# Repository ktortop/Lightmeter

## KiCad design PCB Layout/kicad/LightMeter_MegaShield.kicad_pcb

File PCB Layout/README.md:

# EVEI Light Meter – Arduino Mega 2560 shield (rev B)

Two-layer carrier shield that replaces the hand-wired proto shield. Generated from
`latest_version_of_lightmeter.ino` (pin map) and the Final Design Review slides (part list, wiring), and
checked against the team's current sketch, `Lightmeter_Week8.ino` in this repo (same pins; its `setLED()` sets the LED wiring).
No sketch was modified. Rev B needs a two-line firmware change for the GPS LED (see "Rev B changes"). Rev A is kept in `archive/revA/`.

Board: 90.7 x 102.1 mm with a 1.9 x 14 mm notch over the Mega's barrel jack, 2 layers, 1 oz copper, min track 0.3 mm (signals) / 0.6 mm (power), vias 0.8/0.4 mm (tented), copper at least 0.4 mm from every edge.
ERC: 0 violations. DRC: 0 errors, 0 warnings, 0 unconnected (schematic parity checked).

## Rev B changes

| Change | Detail |
|---|---|
| Second lux sensor port | J10, JST-XH 4 pin, same pinout as LUX1: GND · 5V · SDA · SCL. |
| I2C multiplexer | U3, PCA9548A (SOIC-24W, address 0x70). Needed because the TSL2591 has a fixed address (0x29), so two of them cannot share one bus. LUX2 is on mux channel 0 with 10k pull-ups (R11, R12). |
| Encoder port | J11, JST-XH 4 pin: GND · 5V · A · B. A goes to D2 (INT4), B to D3 (INT5), the two free hardware interrupts. |
| Encoder input conditioning | 10k pull-ups (R14, R15) so open-collector hall encoders work; 1k series + 1nF (R16/C10, R17/C11) filters cable noise and limits current if a pin is ever driven by mistake. |
| GPS status LED moved | D2/D3 to D4/D7, to free the interrupt pins for the encoder. |
| LEDs are common-cathode | Since Week 5 the sketch's `setLED()` drives a die by writing its pin HIGH (YELLOW = both HIGH, OFF = both LOW; the Week 5 comment says this fixed YELLOW and OFF being swapped on the real LEDs). So the LED connectors now give GND on pin 1 (common cathode), and each `*_red` pin drives the red die, each `*_green` pin the green die. All four states (green, red, yellow, off) show correctly with Week 8 as written. Rev A had 5V on pin 1 (common anode), which would have swapped YELLOW and OFF. |
| Barrel-jack notch | The Mega's DC jack (11 mm tall) reaches 0.4 mm under the rev A edge, higher than the 8.5 mm header gap. The bottom-left corner is notched to x = 12.9 mm, and the Mega hole beside the jack is left off (five Mega holes plus H1/H2 remain). |
| Regulator output cap | C2 is a 22 µF tantalum (EIA-3528-B). The AMS1117 needs some output-capacitor ESR to stay stable; a plain ceramic can make it oscillate. |
| SD chip-select pull-up | R18, 10k to 5V on the Mega side of the level shifter, so the card stays deselected while the Mega resets or is being programmed. |
| Nothing under the IMU | Track/via keepout under the BNO055. DC current in nearby traces bends the magnetometer and the heading. Nearest 5V trace is now 11 mm from the IMU centre. |
| Hand-soldering and fab | Thermal reliefs on all ground pads, vias tented, all silkscreen at least 0.15 mm, decoupling caps within 6 mm of their pins. |
| Board size | 13 mm taller (new top row). microSD moved up so its slot is still at the top edge. |

LUX1 stays on the main I2C bus. The mux powers up with every channel off, so LUX1 and the LCD work exactly as before.

### Firmware changes needed (sketch not edited)

1. GPS LED pins, in the constants block:
   ```cpp
   const int gps_red   = 4;   // was 2
   const int gps_green = 7;   // was 3
   ```
   **Make this change before plugging an encoder in.** The old sketch drives D2/D3 as outputs. The 1k series resistors limit the current, but the LED will not work until the pins are changed.

2. Reading the second lux sensor:
   ```cpp
   Adafruit_TSL2591 tsl2 = Adafruit_TSL2591(2592);
   void muxSelect(uint8_t ch) { Wire.beginTransmission(0x70); Wire.write(ch); Wire.endTransmission(); }
   // setup:  muxSelect(0x01); tsl2.begin(); tsl2.setGain(TSL2591_GAIN_LOW); muxSelect(0x00);
   // loop:   muxSelect(0x01); uint32_t lum2 = tsl2.getFullLuminosity(); muxSelect(0x00);
   ```
   Always write 0x00 afterwards. While channel 0 is open, both sensors answer at 0x29.

3. Encoder: D2 and D3 are hardware interrupts, so either `attachInterrupt(digitalPinToInterrupt(2), isrA, CHANGE)` or the PJRC `Encoder` library (`Encoder enc(2, 3);`) works at full speed.

## Folder contents

| Path | What |
|---|---|
| `kicad/` | KiCad 10 project: schematic, PCB, project-local symbol + footprint libs. Open `LightMeter_MegaShield.kicad_pro`. |
| `docs/schematic.pdf` | Schematic (A2, single sheet; rev B additions on the right). |
| `docs/render_top.png`, `render_bottom.png`, `render_3d.png` | 3D renders. |
| `docs/pcb_top.pdf`, `pcb_bottom.pdf` | Copper + silk plots. |
| `docs/BOM.csv` | Bill of materials (grouped). |
| `docs/LightMeter_MegaShield.step` | 3D model for the cart CAD. |
| `fab/LightMeter_MegaShield_gerbers.zip` | Gerbers + Excellon drills, ready for JLCPCB/PCBWay/OSH Park. `-pos.csv` is the SMD pick-and-place file. |
| `generator/` | Python scripts that generated everything (design.py holds the netlist and placement). Re-run if you change a pin. |

## How the Mega is "embedded"

The Arduino Mega 2560 plugs into the underside of this board through the standard Mega
stacking-header pattern (all 92 header and ICSP pads, checked pad by pad against KiCad's own
Arduino Mega template). Five of the Mega's six mounting holes are duplicated on the shield so the two
boards can be bolted together with M3 standoffs. The board is wider than the Mega on top (a
35 mm extension above the top header row) where all the cable connectors and the microSD live,
so no cable crosses the Mega. The left edge stops at x = 11 mm to clear the USB-B jack, and steps to 12.9 mm over the barrel jack.

Plain male headers (see "Assembly and soldering") or a Mega stacking header set both fit. The ICSP pads are on the
footprint but are left unconnected; do not fit a header there.

## What is on the board vs. on a cable

| Function | How | Mega pins (from the sketch) |
|---|---|---|
| Adafruit Ultimate GPS v3 (746) | Soldered onto the board on a 1x9 header (pin order PPS·VIN·GND·RX·TX·FIX·VBAT·EN·3.3V verified from Adafruit's board file) + two M2.5 holes | Serial1: D18→GPS RX, D19←GPS TX |
| microSD | Real socket on the board (Hirose DM3AT push-push), own AMS1117-3.3 regulator (22 µF tantalum output cap), 74LVC125A level shifter on MOSI/SCK/CS, 10k pull-ups on CS/DAT0/DAT1/DAT2 | HW SPI D50/51/52, CS D53 |
| Adafruit BNO055 (2472, non-STEMMA) | Soldered onto the board (1x6 + 1x4 headers, positions from Adafruit's board file) + four M2.5 holes. UART mode: PS1 tied to breakout 3Vo through solder jumper JP1 (bridged by default) | Serial2: D16→BNO SCL pin (UART RX), D17←BNO SDA pin (UART TX) |
| 20x4 LCD (I2C backpack) | J2, JST-XH 4 pin: GND · 5V · SDA · SCL | D20/D21 |
| TSL2591 lux sensor | J3, JST-XH 4 pin: GND · 5V · SDA · SCL (same pinout as LCD, cables interchangeable) | D20/D21 |
| Status LED 1 (GPS) | J4, JST-XH 3 pin: GND (common cathode) · RED · GREEN, 220 Ω series resistors on board | red D4 (`gps_red`), green D7 (`gps_green`) |
| Status LED 2 (LUX) | J5, same | red D5 (`lux_red`), green D6 (`lux_green`) |
| Status LED 3 (IMU) | J6, same | red D8 (`imu_red`), green D9 (`imu_green`) |
| Sleep button | J7, JST-XH 3 pin: GND · SW · 5V (5V for the arcade-button lamp, optional). 100 nF debounce cap on board, uses INPUT_PULLUP | D10 |
| Log-toggle button | J8, same | D11 |
| Force-log button | J9, same | D12 |

LED polarity matches `setLED()` in Week 5-8: output HIGH = die on, both HIGH = yellow, both LOW = off. Wire each LED's common cathode (usually the middle leg of a 3-leg bi-colour LED; check its datasheet) to pin 1, its red leg to pin 2 and its green leg to pin 3, as the silkscreen says (`GND R G`). Two separate red and green LEDs work too: both cathodes to pin 1. Common-anode LEDs will not work on this board.
Buttons go to GND (active LOW), matching `digitalRead(...) == LOW`.

### Cable pinouts (board side is always pin 1 = square pad = left end of the label)

| Port | Pin 1 | Pin 2 | Pin 3 | Pin 4 | Far end |
|---|---|---|---|---|---|
| LCD (J2) | GND | 5V | SDA | SCL | I2C backpack: GND, VCC, SDA, SCL (same order) |
| LUX1 (J3), LUX2 (J10) | GND | 5V | SDA | SCL | Adafruit TSL2591: GND, VIN, SDA, SCL (leave 3Vo and INT unconnected) |
| ENCODER (J11) | GND | 5V | A | B | encoder GND, VCC (5 V encoders only), channel A, channel B |
| GPS/LUX/IMU LED (J4-J6) | GND | red | green | | LED common cathode, red anode, green anode (no resistor needed, 220 Ω is on the board) |
| SLEEP/LOG/FORCE (J7-J9) | GND | SW | 5V | | switch between SW and GND; lamp (optional) between 5V and GND |

**Do not swap LED and button cables.** Both are 3-pin JST-XH, so either fits either port. A button in an LED port is harmless, but an LED in a button port puts 5 V straight onto its green leg with no resistor and burns it out. Label or colour-code the six 3-pin cables. The 4-pin ports are safe to mix up: GND and 5V are on the same pins everywhere.

## Assembly and soldering

Checked against the layout: all parts are on the top side, nothing sits under the GPS or IMU breakouts, no part is in
the path of the Mega header bodies, and the surface-mount parts are all soldered before anything tall goes on
(the closest, R14, is 0.8 mm from C5). Ground pads use thermal reliefs so they take solder with an ordinary iron.
No tracks run under any screw head, washer or standoff. The only pad gap under 0.4 mm is the microSD's unused
card-detect pad (pin 9), left unconnected so a bridge there does no harm.

**Tools:** temperature-controlled iron with a 1–1.6 mm chisel tip, 0.5 mm flux-core solder, a flux pen,
solder wick, fine tweezers, a magnifier or phone camera, a multimeter.

**Headers to buy:** plain male headers are recommended, since nothing stacks on top of this shield:
two 1x40 strips (cut into 1x10, 5 x 1x8) plus one 2x18 (or a 2x20 cut down). They hold the shield
2.5 mm higher than stacking headers do, which adds clearance over the Mega's USB jack, barrel jack and
USB-chip ICSP pins. A "Mega stacking header set" also fits; no part is in the way of either.

### Buy list (not on the BOM)

| Item | Qty | Notes |
|---|---|---|
| Male pin headers, 2.54 mm, 1x40 | 2 | cut into 1x10 + 5 x 1x8 for the Mega |
| Male pin header, 2.54 mm, 2x18 (or 2x20 cut down) | 1 | Mega double row |
| M2.5 nylon hex standoffs, 5 mm | 2 | GPS (the coin-cell holder needs the height) |
| M2.5 nylon screws, 6 mm | 4 | GPS (2 standoffs, both ends) |
| M2.5 nylon screws + nuts | 4 | IMU (optional, the headers hold it) |
| M3 nylon standoffs, 11 mm, + screws | up to 5 | Mega to shield (optional); 11 mm = 8.5 mm female header + 2.5 mm male header spacer |
| JST-XH housings XHP-4 / XHP-3 | 4 / 6 | cable ends |
| JST-XH crimp contacts SXH-001T-P0.6 | about 40 | needs a JST-type crimper (for example Engineer PA-09); pre-crimped XH leads avoid the tool |
| 5 mm bi-colour red/green LED, common cathode | 3 | or separate red + green LEDs |
| microSD card, 32 GB or less, FAT32 | 1 | the SD library only reads FAT16/FAT32 |
| CR1220 coin cell | 1 | optional, keeps the GPS almanac for faster fixes |

### Solder order (smallest and hardest first)

1. **microSD socket (J1).** Hardest joint: 8 pins at 1.1 mm pitch that stick out only 0.5 mm past the
   metal shell. Flux the pads, place the socket, tack one shell tab, check alignment, solder all four shell
   tabs, then touch each signal pin with the tip of the iron. Inspect for bridges and wick any away.
2. **SOIC chips, U1 (74LVC125A) and U3 (PCA9548A).** Match the dot on the chip to the pin-1 mark on the
   silkscreen. Tack one corner pin, check both rows are on their pads, solder the opposite corner, then
   the rest. Flux and wick fix bridges.
3. **Regulator U2 (AMS1117, SOT-223).** The large tab needs more heat: use a bigger tip or more dwell time.
4. **0805 resistors and capacitors.** Do one value at a time from the BOM: 220 Ω (R1–R6), 10 kΩ
   (R7–R15, R18), 1 kΩ (R16, R17), 100 nF (C3, C4, C6–C9), 1 nF (C10, C11), 10 µF (C1). Tin one pad,
   slide the part in with tweezers, then solder the other end.
5. **C2 tantalum.** Polarized: the stripe on the part goes to the side marked on the silkscreen (+3.3 V).
6. **Short test before anything else.** With the multimeter, check there is no short between 5V and GND,
   or between 3.3V and GND. It is much easier to fix now.
7. **C5 electrolytic** (100 µF/16 V, 6.3 mm or 5 mm diameter). Long leg (+) to the square pad, stripe (–) to the round pad.
8. **JST connectors J2–J11.** Push fully down; the outline on the silkscreen shows which way the housing faces.
9. **Mega headers.** Plug the headers into the Mega first, lay the shield on top, then solder from the top.
   This guarantees they line up with the Mega. Unplug the shield before the next steps.
10. **GPS breakout.** The CR1220 holder on the GPS's underside is taller than a header's 2.5 mm plastic spacer, so
    the GPS sits on 5 mm standoffs. Screw the two 5 mm nylon standoffs to the shield (holes at the far end from the
    header). Push the **short** pins of the 1x9 header up into the GPS from below (plastic spacer against the GPS),
    lower the long pins through the shield, screw the GPS to the standoffs, then solder on top of the GPS and under
    the shield. About 1.9 mm of pin comes through the shield. Antenna (ceramic patch) faces up.
11. **IMU breakout.** Nothing on its underside, so the headers' own 2.5 mm spacers set the height: short pins into
    the IMU (1x6 and 1x4), long pins through the shield, solder both ends. Nylon hardware only if you add screws
    (steel or brass near the magnetometer affects the heading). The +X arrow on the BNO055 must point along
    the cart's direction of travel when the board is mounted.
12. **Trim** the GPS and IMU header pins that stick out under the shield flush, so they cannot touch the Mega.
    Do **not** trim the Mega header pins: they are what plugs into the Mega.

JP1 needs no soldering: it ships bridged by a copper trace. Only cut it to move the IMU to I2C.

### First power-up

1. No cables plugged in. Connect the Mega to USB. Measure 5 V on any JST pin 2 (LCD/LUX) and 3.3 V on C4.
2. Feel U2, U1 and U3: none should be warm.
3. Change `gps_red = 4` and `gps_green = 7` in the sketch, upload, then plug in the LEDs, LCD, lux
   sensor and buttons. Insert the SD card last.
4. Expected at boot (Week 8): all three LEDs red; IMU turns green when the BNO055 answers, GPS turns yellow while it
   waits for a fix, LUX turns green when the TSL2591 answers.

### Other notes

- IMU orientation matters. Week 8's level check uses roll only (`eulY`, rotation about the BNO's Y axis), and the
  heading and forward acceleration (`linX`) assume the BNO's +X axis points along the cart's travel. Mount the board
  so the +X arrow printed on the BNO055 breakout points forward (the shield silkscreen says so). If the board has to be
  mounted 90° off, swap roll and pitch (and use `linY`) in the sketch instead.
- MISO comes back to D50 at 3.3 V without shifting, the same as the Adafruit SD breakout used today. The ATmega2560
  reads HIGH from 3.0 V, so the margin is small; real cards drive close to 3.3 V at this light load. If a card is
  flaky, try another brand before suspecting the board.
- Power budget from the Mega's 5 V rail: Mega about 80 mA, 20x4 LCD backlight about 100 mA, LEDs up to 80 mA (all
  yellow), SD card up to 100 mA while writing, GPS 30 mA, BNO055 12 mA, encoder and button lamps 20-60 mA:
  about 400-450 mA worst case. USB (500 mA fuse) or a 5 V supply into USB is fine. On the barrel jack use about 7 V:
  at 9 V the Mega's regulator dissipates about 1.8 W and will overheat.

## Design decisions / assumptions worth reviewing

- "Embedded Arduino" was implemented as a shield the Mega plugs into, not a bare ATmega2560 on
  the board. That keeps the USB bootloader, uses the Mega the team already has and is buildable
  by hand. A bare-chip version could follow once this one is proven.
- The IMU was placed on the board (not on a connector) because it must be rigidly fixed to the
  cart for the tilt check and it removes six jumper wires. If you want it remote, the header
  footprint accepts a cable instead.
- The Adafruit MicroSD breakout was replaced by an on-board socket and level shifter (its own
  circuit, copied). The Adafruit breakout is no longer needed.
- The cart-facing connectors are JST-XH because they lock and are cheap; the pin-order note is on
  the silkscreen next to every connector.
- Board outline, stacking-header positions and breakout footprints are from published board
  files, but nothing has been test-fitted physically. Print `docs/pcb_top.pdf` 1:1 and lay the
  Mega, the GPS and the IMU on it before ordering.

## Pre-order validation (final)

Automated: ERC 0, DRC 0 errors / 0 warnings, 0 unconnected, schematic-parity 0, netlist matches `generator/design.py` on all 42 nets.
`generator/audit.py` re-checks edge clearances, annular rings, decoupling distances, the IMU keepout and the LED mapping.

Against OSH Park's 2-layer rules: track 0.30 mm (min 0.152), clearance 0.20 mm (min 0.152), drill 0.40 mm (min 0.33),
annular ring 0.20 mm (min 0.178), copper to edge 0.40 mm (min 0.38). Gerber mask and drill files cross-checked against the board:
274 pad openings, 199 plated holes (147 pins + 52 vias), 13 unplated holes.
A second pass also ran DRC with every check enabled (only the expected Mega "no courtyard" and the 74LVC125 symbol's
DIP-only footprint filter came up), checked every net pin by pin against `design.py`, and checked the GPS, BNO055 and
Mega footprints against Adafruit's board files and KiCad's Arduino Mega template.

Check during the 1:1 paper test-fit, because only the physical parts can confirm them:
- the Mega's barrel jack clears the notch and the USB jack clears the left edge;
- the 6-pin ICSP header of the Mega's USB chip (near the USB jack) does not touch the underside (plain male headers give 2.5 mm more room; tape it if it touches);
- the GPS and IMU header pins are trimmed flush underneath so they cannot touch the Mega.

Not board issues, but decide before use:
- Power the Mega from USB (a USB power bank works) or about 7 V on the barrel jack; 9 V and above overheat its regulator at this load.
- Use nylon standoffs and screws near the IMU, not steel or brass.
- Long I2C cables to the LCD and lux sensors (over about 1 m) may need slower I2C (`Wire.setClock(50000)`).
- Arcade-button lamps are often rated 12 V; at 5 V they are dim but safe.

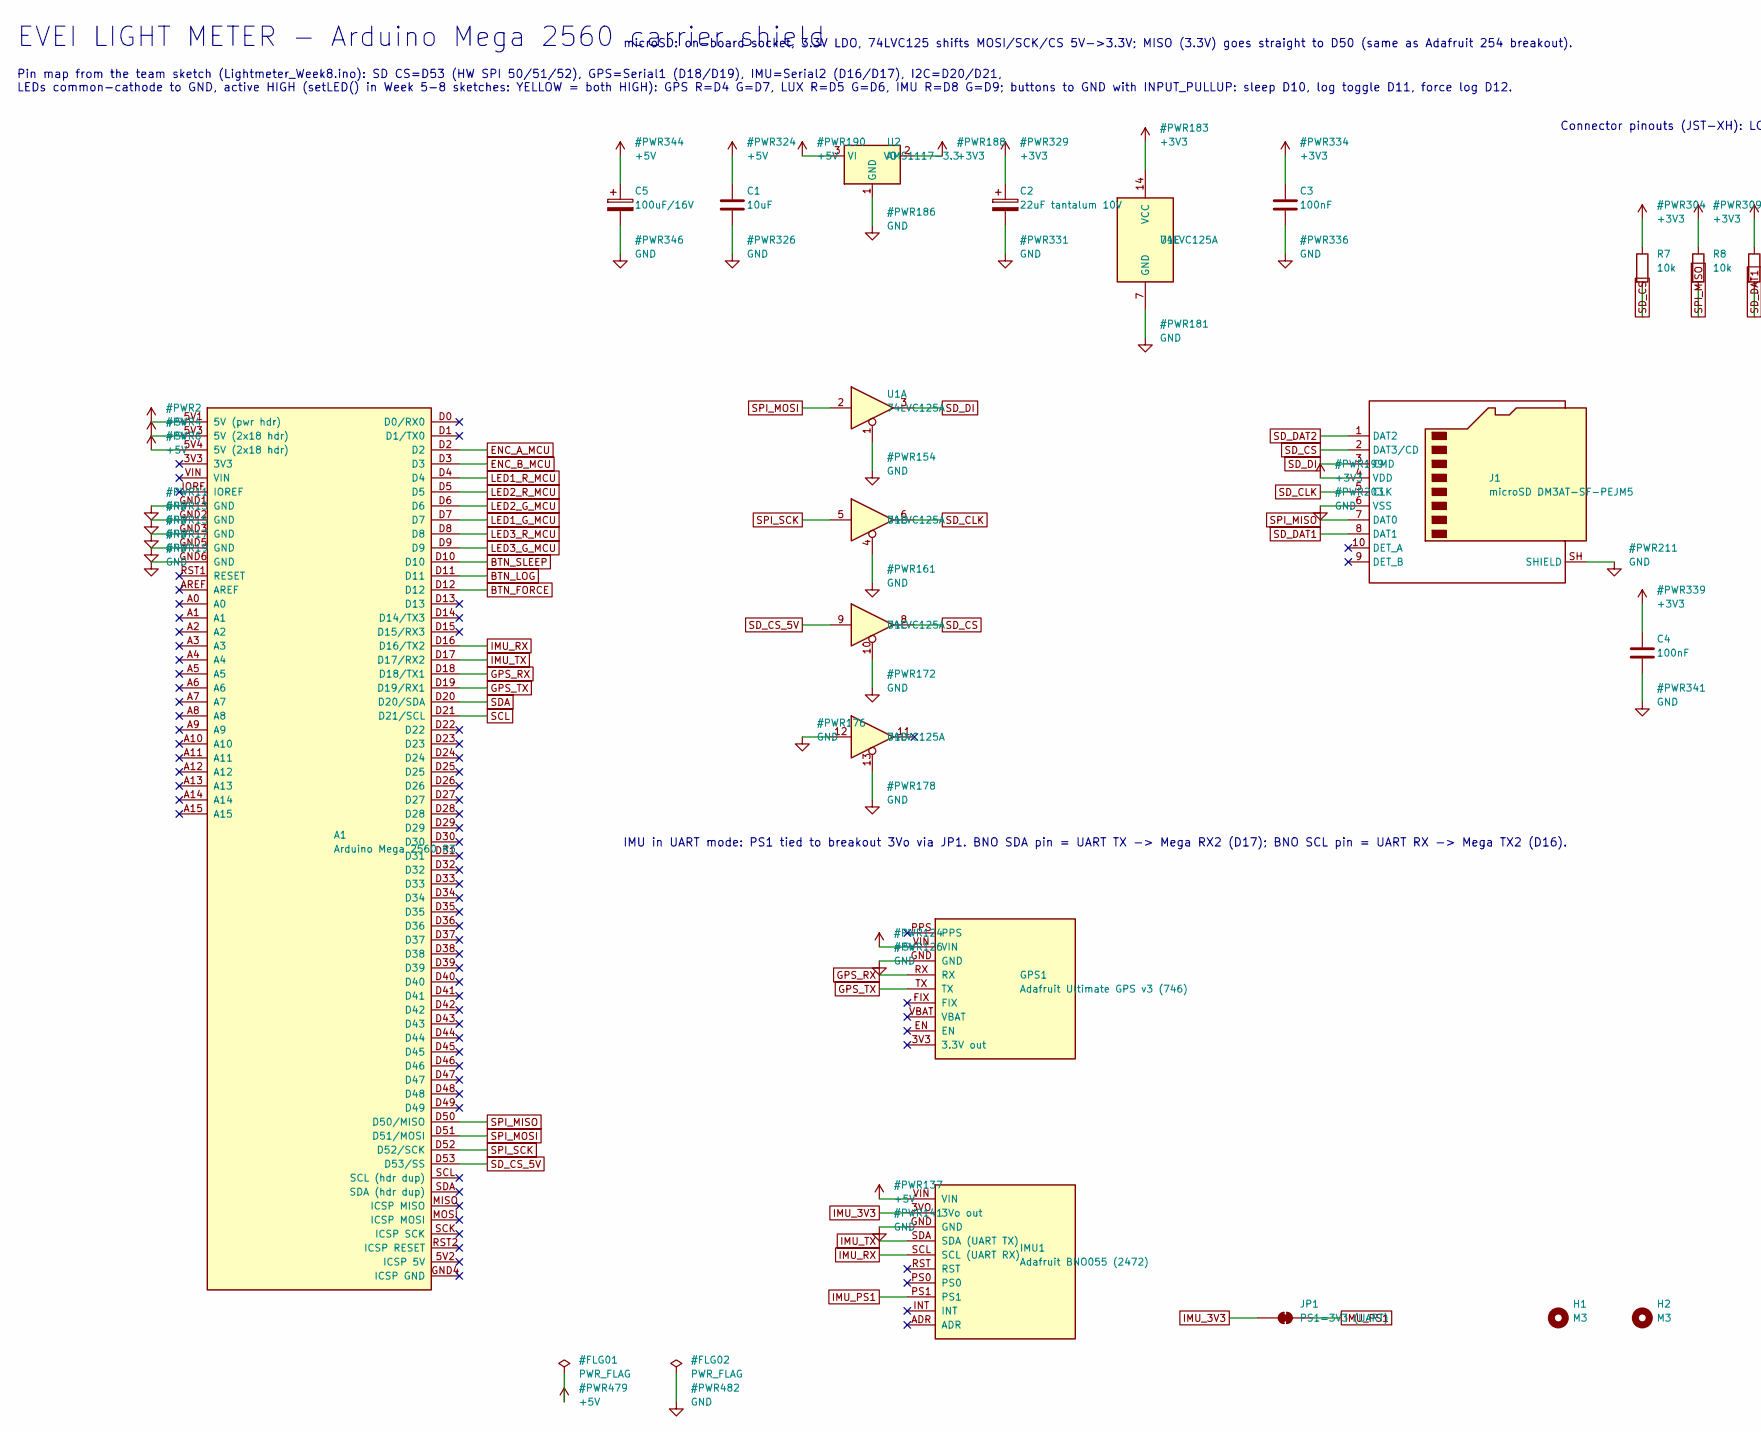
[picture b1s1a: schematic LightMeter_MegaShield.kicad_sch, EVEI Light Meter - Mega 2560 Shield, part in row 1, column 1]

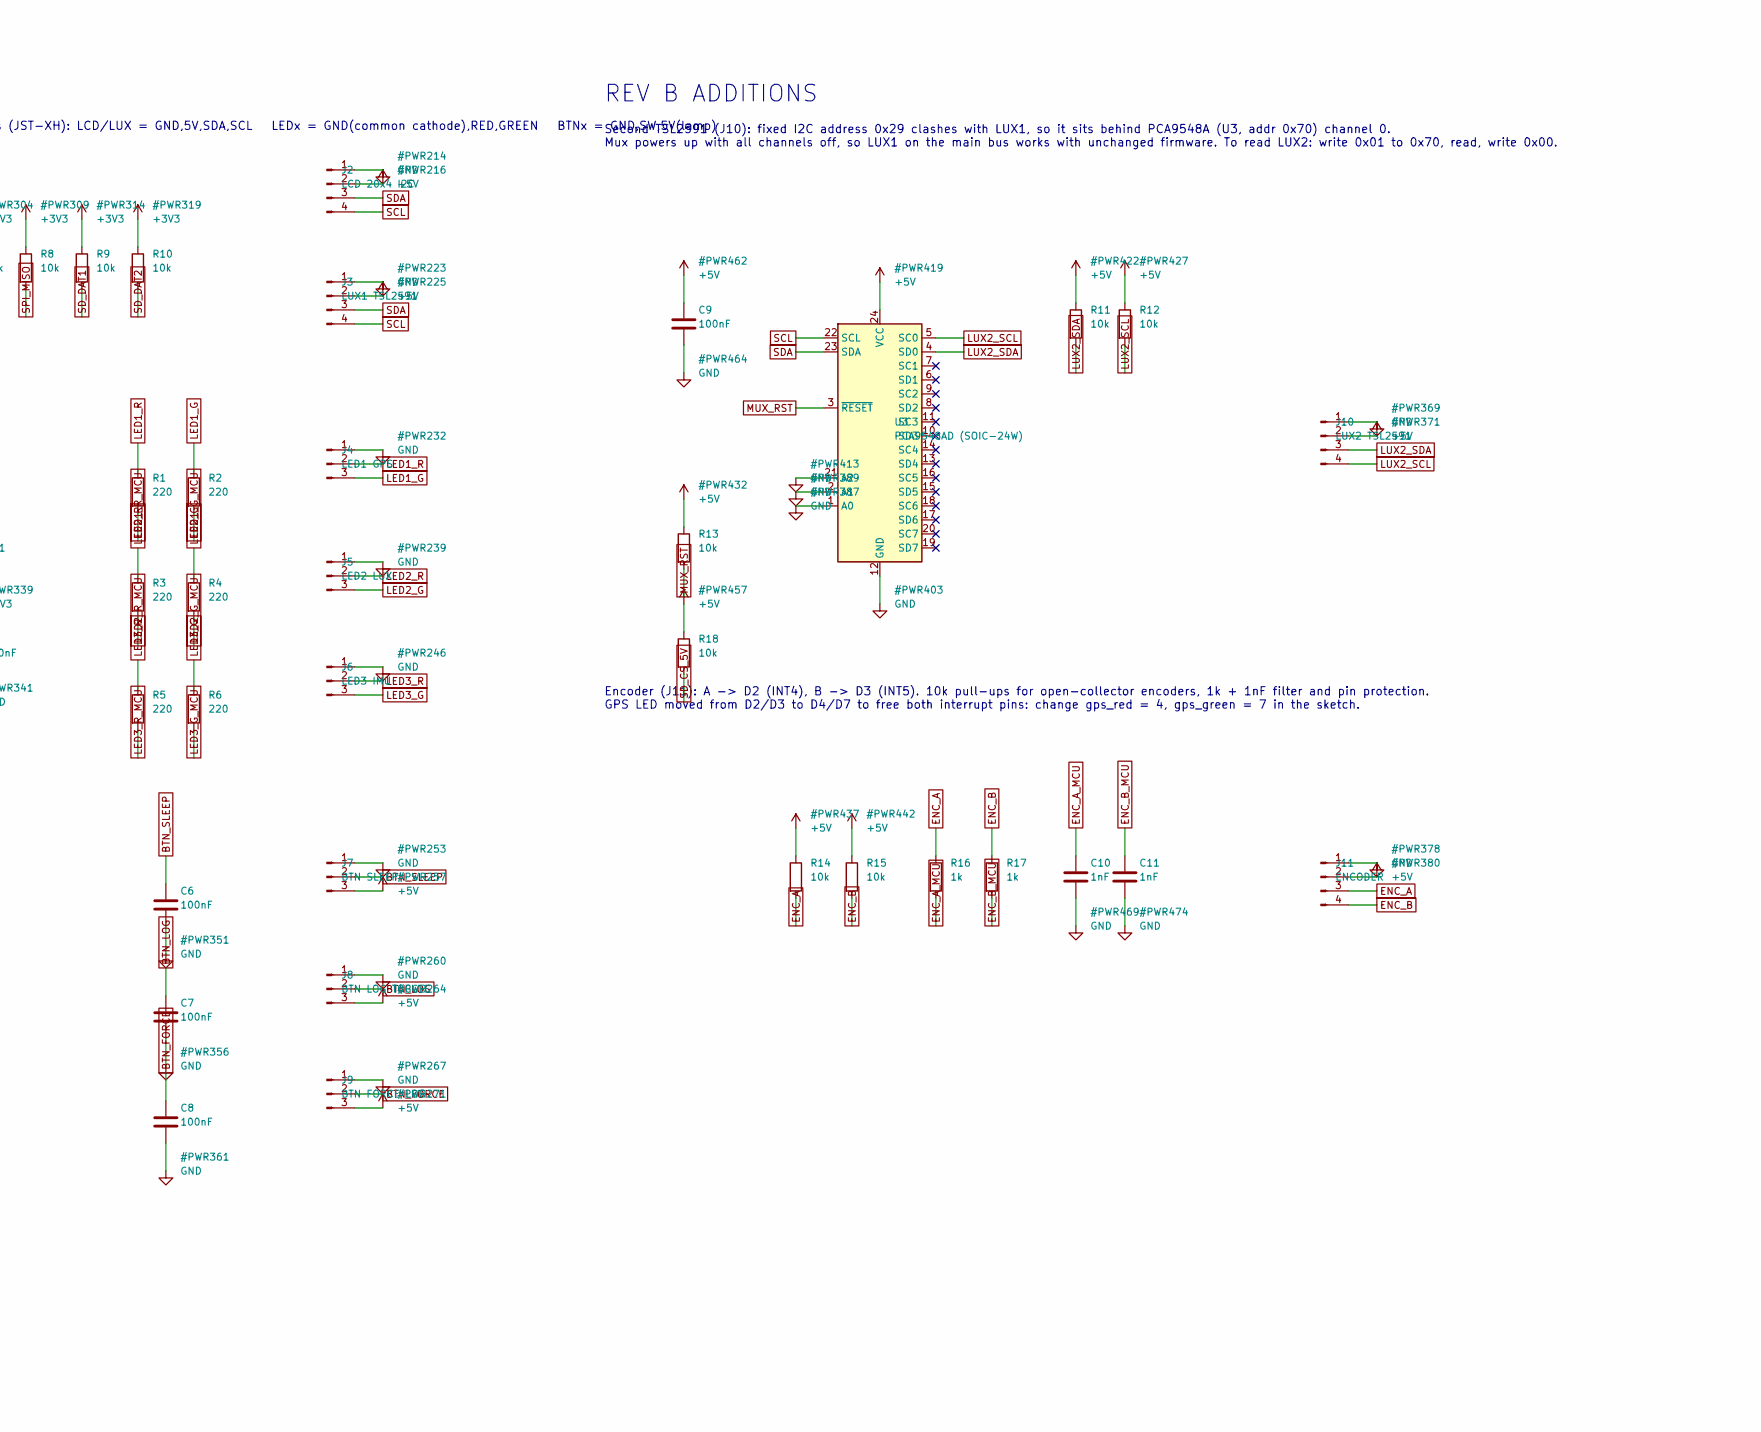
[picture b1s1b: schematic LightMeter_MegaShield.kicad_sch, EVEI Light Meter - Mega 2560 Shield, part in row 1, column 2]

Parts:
A1: Arduino Mega 2560 R3; Arduino_Mega2560_Shield
C1: 10uF; C_0805_2012Metric
C2: 22uF tantalum 10V; CP_EIA-3528-21_Kemet-B
C3, C4, C6, C7, C8, C9: 100nF; C_0805_2012Metric
C5: 100uF/16V; CP_Radial_D6.3mm_P2.50mm
C10, C11: 1nF; C_0805_2012Metric
GPS1: Adafruit Ultimate GPS v3 (746); Adafruit_UltimateGPS_v3
H1, H2: M3; MountingHole_3.2mm_M3
IMU1: Adafruit BNO055 (2472); Adafruit_BNO055_2472
J1: microSD DM3AT-SF-PEJM5; microSD_HC_Hirose_DM3AT-SF-PEJM5
J2: LCD 20x4 I2C; JST_XH_B4B-XH-A_1x04_P2.50mm_Vertical
J3: LUX1 TSL2591; JST_XH_B4B-XH-A_1x04_P2.50mm_Vertical
J4: LED1 GPS; JST_XH_B3B-XH-A_1x03_P2.50mm_Vertical
J5: LED2 LUX; JST_XH_B3B-XH-A_1x03_P2.50mm_Vertical
J6: LED3 IMU; JST_XH_B3B-XH-A_1x03_P2.50mm_Vertical
J7: BTN SLEEP; JST_XH_B3B-XH-A_1x03_P2.50mm_Vertical
J8: BTN LOG TOGGLE; JST_XH_B3B-XH-A_1x03_P2.50mm_Vertical
J9: BTN FORCE LOG; JST_XH_B3B-XH-A_1x03_P2.50mm_Vertical
J10: LUX2 TSL2591; JST_XH_B4B-XH-A_1x04_P2.50mm_Vertical
J11: ENCODER; JST_XH_B4B-XH-A_1x04_P2.50mm_Vertical
JP1: PS1=3V3 (UART); SolderJumper-2_P1.3mm_Bridged_RoundedPad1.0x1.5mm
R1, R2, R3, R4, R5, R6: 220; R_0805_2012Metric
R7, R8, R9, R10, R11, R12, R13, R14, R15, R18: 10k; R_0805_2012Metric
R16, R17: 1k; R_0805_2012Metric
U1: 74LVC125A; SOIC-14_3.9x8.7mm_P1.27mm
U2: AMS1117-3.3; SOT-223-3_TabPin2
U3: PCA9548AD (SOIC-24W); SOIC-24W_7.5x15.4mm_P1.27mm

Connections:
+3V3: C2.1, C3.1, C4.1, J1.4 (VDD), R7.1, R8.1, R9.1, R10.1, U1.14 (VCC), U2.2 (VO)
+5V: A1.5V1 (5V (pwr hdr)), A1.5V3 (5V (2x18 hdr)), A1.5V4 (5V (2x18 hdr)), C1.1, C5.1, C9.1, GPS1.VIN, IMU1.VIN, J2.2, J3.2, J7.3, J8.3, J9.3, J10.2, J11.2, R11.1, R12.1, R13.1, R14.1, R15.1, R18.1, U2.3 (VI), U3.24 (VCC)
BTN_FORCE: A1.D12, C8.1, J9.2
BTN_LOG: A1.D11, C7.1, J8.2
BTN_SLEEP: A1.D10, C6.1, J7.2
ENC_A: J11.3, R14.2, R16.1
ENC_A_MCU: A1.D2, C10.1, R16.2
ENC_B: J11.4, R15.2, R17.1
ENC_B_MCU: A1.D3, C11.1, R17.2
GND: A1.GND1 (GND), A1.GND2 (GND), A1.GND3 (GND), A1.GND5 (GND), A1.GND6 (GND), C1.2, C2.2, C3.2, C4.2, C5.2, C6.2, C7.2, C8.2, C9.2, C10.2, C11.2, GPS1.GND, IMU1.GND, J1.6 (VSS), J1.SH (SHIELD), J2.1, J3.1, J4.1, J5.1, J6.1, J7.1, J8.1, J9.1, J10.1, J11.1, U1.1, U1.4, U1.7 (GND), U1.10, U1.12, U1.13, U2.1 (GND), U3.1 (A0), U3.2 (A1), U3.12 (GND), U3.21 (A2)
GPS_RX: A1.D18 (D18/TX1), GPS1.RX
GPS_TX: A1.D19 (D19/RX1), GPS1.TX
IMU_3V3: IMU1.3VO (3Vo out), JP1.1 (A)
IMU_PS1: IMU1.PS1, JP1.2 (B)
IMU_RX: A1.D16 (D16/TX2), IMU1.SCL (SCL (UART RX))
IMU_TX: A1.D17 (D17/RX2), IMU1.SDA (SDA (UART TX))
LED1_G: J4.3, R2.1
LED1_G_MCU: A1.D7, R2.2
LED1_R: J4.2, R1.1
LED1_R_MCU: A1.D4, R1.2
LED2_G: J5.3, R4.1
LED2_G_MCU: A1.D6, R4.2
LED2_R: J5.2, R3.1
LED2_R_MCU: A1.D5, R3.2
LED3_G: J6.3, R6.1
LED3_G_MCU: A1.D9, R6.2
LED3_R: J6.2, R5.1
LED3_R_MCU: A1.D8, R5.2
LUX2_SCL: J10.4, R12.2, U3.5 (SC0)
LUX2_SDA: J10.3, R11.2, U3.4 (SD0)
MUX_RST: R13.2, U3.3 (~RESET)
SCL: A1.D21 (D21/SCL), J2.4, J3.4, U3.22 (SCL)
SDA: A1.D20 (D20/SDA), J2.3, J3.3, U3.23 (SDA)
SD_CLK: J1.5 (CLK), U1.6
SD_CS: J1.2 (DAT3/CD), R7.2, U1.8
SD_CS_5V: A1.D53 (D53/SS), R18.2, U1.9
SD_DAT1: J1.8 (DAT1), R9.2
SD_DAT2: J1.1 (DAT2), R10.2
SD_DI: J1.3 (CMD), U1.3
SPI_MISO: A1.D50 (D50/MISO), J1.7 (DAT0), R8.2
SPI_MOSI: A1.D51 (D51/MOSI), U1.2
SPI_SCK: A1.D52 (D52/SCK), U1.5

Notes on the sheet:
EVEI LIGHT METER - Arduino Mega 2560 carrier shield
Pin map from the team sketch (Lightmeter_Week8.ino): SD CS=D53 (HW SPI 50/51/52), GPS=Serial1 (D18/D19), IMU=Serial2 (D16/D17), I2C=D20/D21, LEDs common-cathode to GND, active HIGH (setLED() in Week 5-8 sketches: YELLOW = both HIGH): GPS R=D4 G=D7, LUX R=D5 G=D6, IMU R=D8 G=D9; buttons to GND with 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
microSD: on-board socket, 3.3V LDO, 74LVC125 shifts MOSI/SCK/CS 5V->3.3V; MISO (3.3V) goes straight to D50 (same as Adafruit 254 breakout).
IMU in UART mode: PS1 tied to breakout 3Vo via JP1. BNO SDA pin = UART TX -> Mega RX2 (D17); BNO SCL pin = UART RX -> Mega TX2 (D16).
REV B ADDITIONS
Second TSL2591 (J10): fixed I2C address 0x29 clashes with LUX1, so it sits behind PCA9548A (U3, addr 0x70) channel 0. Mux powers up with all channels off, so LUX1 on the main bus works with unchanged firmware. To read LUX2: write 0x01 to 0x70, read, write 0x00.
Encoder (J11): A -> D2 (INT4), B -> D3 (INT5). 10k pull-ups for open-collector encoders, 1k + 1nF filter and pin protection. GPS LED moved from D2/D3 to D4/D7 to free both interrupt pins: change gps_red = 4, gps_green = 7 in the sketch.
Connector pinouts (JST-XH): LCD/LUX = GND,5V,SDA,SCL LEDx = GND(common cathode),RED,GREEN BTNx = GND,SW,5V(lamp)

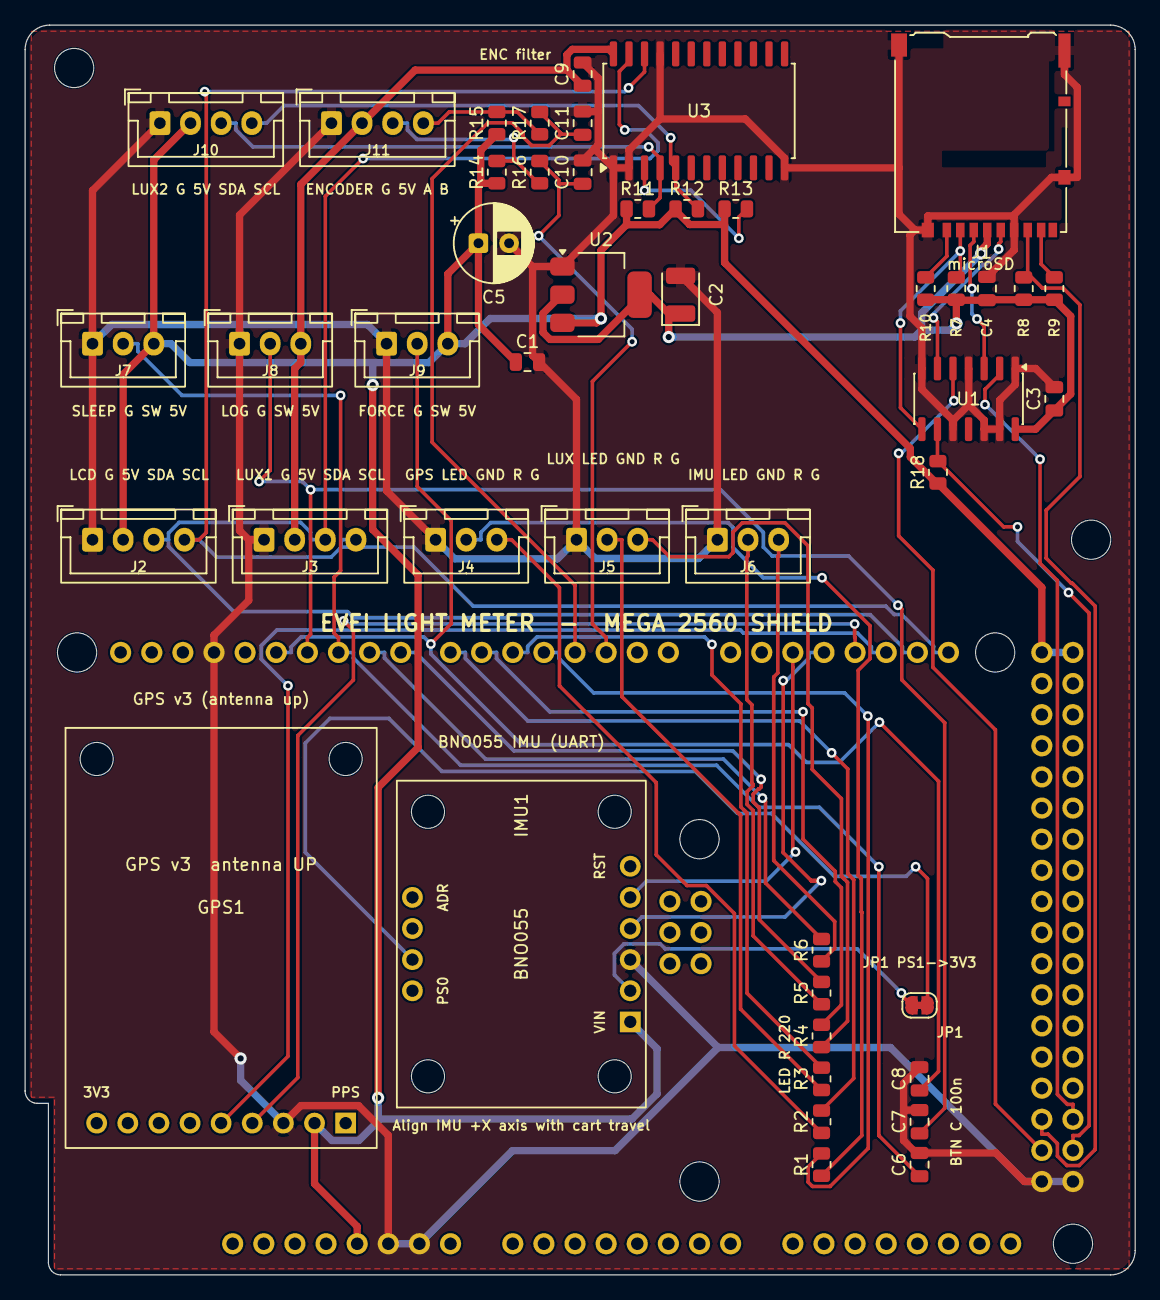
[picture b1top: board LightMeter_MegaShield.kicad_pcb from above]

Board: 2 copper layers, 90.6 x 102.0 mm, 49 parts (0 on the bottom side), 42 nets.

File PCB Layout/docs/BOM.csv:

"Refs","Value","Footprint","Description","Qty"
"A1","Arduino Mega 2560 R3","LightMeter:Arduino_Mega2560_Shield","Arduino Mega 2560 (shield headers, board plugs on top)","1"
"C1","10uF","Capacitor_SMD:C_0805_2012Metric","LDO input","1"
"C2","22uF tantalum 10V","Capacitor_Tantalum_SMD:CP_EIA-3528-21_Kemet-B","LDO output; tantalum ESR keeps AMS1117 stable","1"
"C3,C4,C6-C9","100nF","Capacitor_SMD:C_0805_2012Metric","BTN force debounce,BTN log debounce,BTN sleep debounce,SD VDD decoupling,U1 decoupling,U3 decoupling","6"
"C5","100uF/16V","Capacitor_THT:CP_Radial_D6.3mm_P2.50mm","5V bulk, 6.3 mm radial, 2.5 mm pitch (5 mm parts fit too)","1"
"C10,C11","1nF","Capacitor_SMD:C_0805_2012Metric","encoder A filter, 1 us with R16,encoder B filter","2"
"GPS1","Adafruit Ultimate GPS v3 (746)","LightMeter:Adafruit_UltimateGPS_v3","GPS breakout soldered to board via 1x9 header","1"
"IMU1","Adafruit BNO055 (2472)","LightMeter:Adafruit_BNO055_2472","IMU breakout soldered to board, UART mode","1"
"J1","microSD DM3AT-SF-PEJM5","Connector_Card:microSD_HC_Hirose_DM3AT-SF-PEJM5","microSD socket, push-push","1"
"J2","LCD 20x4 I2C","Connector_JST:JST_XH_B4B-XH-A_1x04_P2.50mm_Vertical","JST-XH 4p: GND 5V SDA SCL","1"
"J3","LUX1 TSL2591","Connector_JST:JST_XH_B4B-XH-A_1x04_P2.50mm_Vertical","JST-XH 4p: GND 5V SDA SCL","1"
"J4","LED1 GPS","Connector_JST:JST_XH_B3B-XH-A_1x03_P2.50mm_Vertical","JST-XH 3p: GND(common cathode) R G","1"
"J5","LED2 LUX","Connector_JST:JST_XH_B3B-XH-A_1x03_P2.50mm_Vertical","JST-XH 3p: GND(common cathode) R G","1"
"J6","LED3 IMU","Connector_JST:JST_XH_B3B-XH-A_1x03_P2.50mm_Vertical","JST-XH 3p: GND(common cathode) R G","1"
"J7","BTN SLEEP","Connector_JST:JST_XH_B3B-XH-A_1x03_P2.50mm_Vertical","JST-XH 3p: GND SW 5V(lamp)","1"
"J8","BTN LOG TOGGLE","Connector_JST:JST_XH_B3B-XH-A_1x03_P2.50mm_Vertical","JST-XH 3p: GND SW 5V(lamp)","1"
"J9","BTN FORCE LOG","Connector_JST:JST_XH_B3B-XH-A_1x03_P2.50mm_Vertical","JST-XH 3p: GND SW 5V(lamp)","1"
"J10","LUX2 TSL2591","Connector_JST:JST_XH_B4B-XH-A_1x04_P2.50mm_Vertical","JST-XH 4p: GND 5V SDA SCL (behind I2C mux ch0)","1"
"J11","ENCODER","Connector_JST:JST_XH_B4B-XH-A_1x04_P2.50mm_Vertical","JST-XH 4p: GND 5V A B, quadrature encoder","1"
"R1-R6","220","Resistor_SMD:R_0805_2012Metric","LED1 green series,LED1 red series,LED2 green series,LED2 red series,LED3 green series,LED3 red series","6"
"R7-R15,R18","10k","Resistor_SMD:R_0805_2012Metric","LUX2 SCL pull-up,LUX2 SDA pull-up,SD CS pull-up,SD CS pull-up, Mega side (card deselected during reset),SD DAT0/MISO pull-up,SD DAT1 pull-up,SD DAT2 pull-up,encoder A pull-up (open-collector outputs),encoder B pull-up,mux RESET pull-up","10"
"R16,R17","1k","Resistor_SMD:R_0805_2012Metric","encoder A series (filter + pin protection),encoder B series","2"
"U1","74LVC125A","Package_SO:SOIC-14_3.9x8.7mm_P1.27mm","5V->3.3V level shifter for SD MOSI/SCK/CS","1"
"U2","AMS1117-3.3","Package_TO_SOT_SMD:SOT-223-3_TabPin2","3.3V LDO for microSD","1"
"U3","PCA9548AD (SOIC-24W)","Package_SO:SOIC-24W_7.5x15.4mm_P1.27mm","I2C mux, addr 0x70; ch0 = second TSL2591 (same 0x29 address)","1"

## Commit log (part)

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2026-01-27 original file
2026-01-27 changed baud rate to 9600
2026-01-27 Removed dependancy on microsd, test outside
2026-01-27 added somestuff
    Added comments for future reference, testing, and TODOs. Improved handling of GPS data.
2026-01-29 screen update, not tested
2026-02-01 Battery display - not tested
2026-02-01 Battery display - not tested V2
2026-02-01 removed sd; working gps and lux
2026-02-05 please don't delete anything on here
2026-02-05 Implement SD card logging and enhance comments
    Added SD card logging functionality for testing and improved comments regarding GPS data handling.
2026-02-12 some tweaks, didn't change anything
2026-02-12 Rename LightMeter2_BASIC.ino to LightMeter2_BASIC./LightMeter2_BASIC.ino
2026-02-12 Rename LightMeter2_BASIC.ino to LightMeter2_BASIC.ino
2026-02-12 LED code, commented out
2026-03-05 Just making sure things are updated
2026-03-05 IMU CODE
    Added GPS-based tracking and improved isMoving function to enhance distance measurement and velocity calculations.
2026-03-05 extra code removed
    Removed unused battery voltage calculations, GPS data logging, and display code.
2026-03-05 New code with Lux Averaging
2026-03-05 New Lux Sensor Code, not tested
2026-03-08 Just some naming conventions, lux sensor updating not tested yet
2026-03-08 IMU location error, not tested
2026-03-12 Check if cart level
2026-03-12 Goated code
2026-03-25 if I broke anything I'll revert it
2026-03-26 added outlier display
2026-03-29 Add IMU LED
    imu red is 7, imu green is 8
